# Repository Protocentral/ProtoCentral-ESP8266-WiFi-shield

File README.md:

ProtoCentral ESP8266 WiFi shield 
==================================
 [  
*ProtoCentral ESP8266 WiFi shield (PC-4356)*](https://www.protocentral.com/arduino-shields/944-protocentral-esp8266-wifi-shieldstandalone-for-arduino.html)
 
The ESP8266 WiFi chip has taken the IoT world by storm by breaking the cost barrier and making the IoT truly possible. The ProtoCentral ESP8266 WiFi shield is an easy and quick way to add WiFi functionality to your Arduino.
This board can be used an Arduino shield as well as a standalone breakout board if you prefer to program the ESP8266 directly. The onboard FT230X USB-to-UART circuit allows direct access to to the ESP 8266 module's UART interface. This allows programming of the ESP8266 chip's onboard processor to run the application itself without the need for an Arduino.
The module comes pre-flashed with the ESP8266 AT command set firmware. 

Features Overload!
-------------------
*	Slide switch - Serial communication support to work on ESP module individually
*	Firmware upgrade for ESP through USB
*	On board FTDI
*	Onboard regulator 3.3v with 800mA
*	Can be powered on/off using USB or from the Arduino board 
*	Board is pre-flashed  with an AT command set firmware and the same can be used to control ESP8266 module
*	Extra ESP8266 pins broken out for any additional usage requirements
*	802.11 b/g/n
*	Wi-Fi Direct (P2P), soft-AP
*	Integrated TCP/IP protocol stack

Includes:
----------
* Shield with the headers

Repository Contents
-------------------
* **/Firmware**  - Firmware and bin files for ESP8266
* **/Libraries** - Arduino library and example sketches.
* **/Hardware**  - All Eagle design files (.brd, .sch)

License Information
-------------------
This product is open source!

Please use, reuse, and modify these files as you see fit. Please maintain attribution to Protocentral and release anything derivative under the same license.

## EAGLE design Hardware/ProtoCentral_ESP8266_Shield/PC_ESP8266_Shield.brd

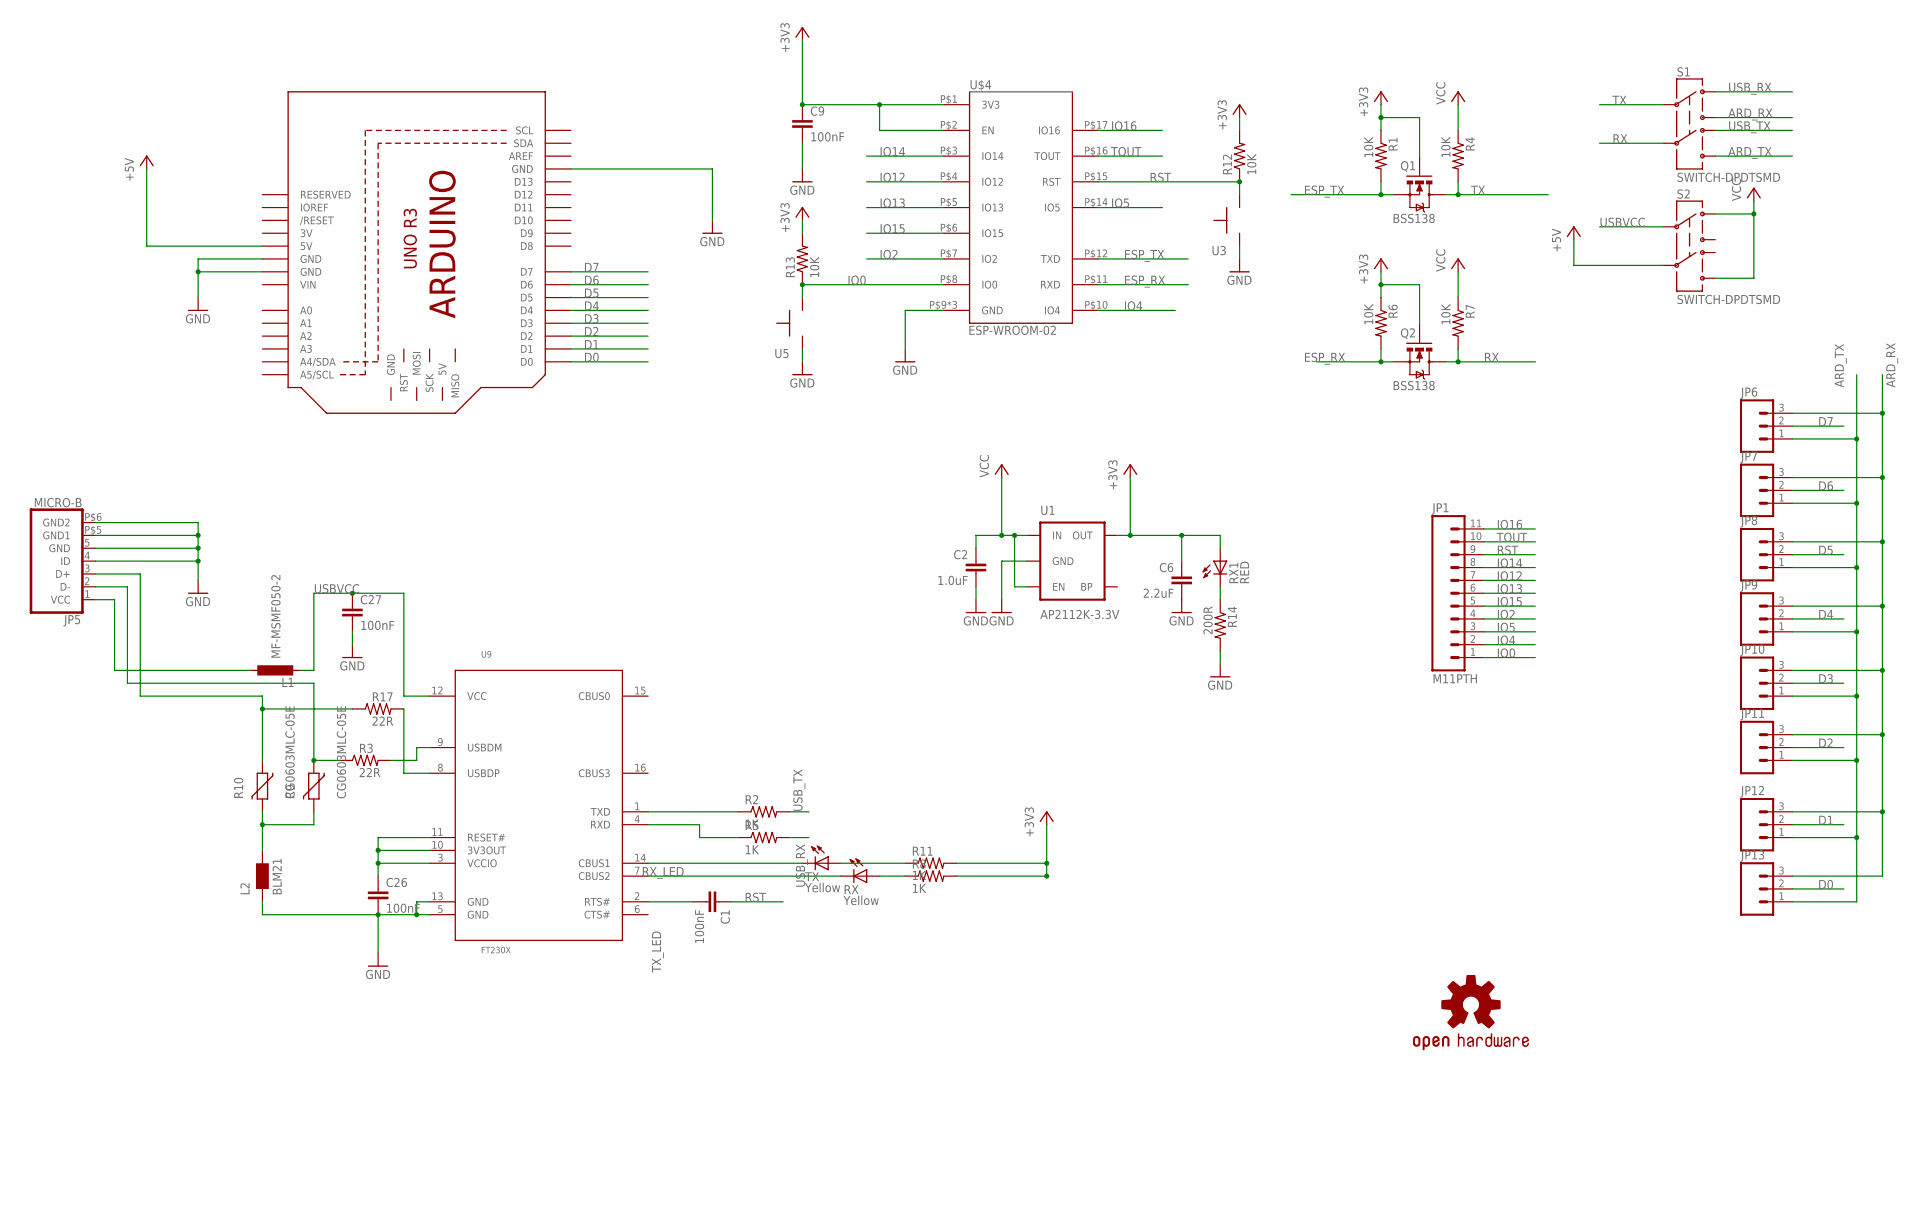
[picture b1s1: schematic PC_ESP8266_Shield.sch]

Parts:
C1, C9, C26, C27: 100nF; C0805
C2: 1.0uF; 0805
C6: 2.2uF; C0805
JP1: M11PTH; 1X11
JP5: MICRO-B
JP6, JP7, JP8, JP9, JP10, JP11, JP12, JP13: M03PTH; 1X03
L1: MF-MSMF050-2; L1812
L2: BLM21; 0805
Q1, Q2: BSS138; SOT23-3
R1, R4, R6, R7, R12, R13: 10K; R0805
R2, R5, R8, R11: 1K; R0805
R3, R17: 22R; R0805
R9, R10: CG0603MLC-05E; CT/CN0603
R14: 200R; R0805
RX: Yellow; CHIPLED_0603
RX1: RED; CHIPLED_0603
S1, S2: SWITCH-DPDTSMD; AYZ0202
TX: Yellow; CHIPLED_0603
U1: AP2112K-3.3V; SOT23-5
U3, U5: B3U-1000P
U9: FT230X; SSOP_16
U$1: ARDUINO
U$3: PROTY-LOGO; LOGO-PROTY
U$4: ESP-WROOM-02
U$5: OSHW-LOGOS; OSHW-LOGO-S

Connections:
3V: U$1.3V
+3V3: C6.1, C9.1, Q1.1 (G), Q2.1 (G), R1.1, R6.1, R8.2, R11.2, R12.2, R13.2, RX1.A, U1.5 (OUT), U$4.P$1 (3V3), U$4.P$2 (EN)
+5V: S2.5, U$1.5V
ARD_RX: JP6.3, JP7.3, JP8.3, JP9.3, JP10.3, JP11.3, JP12.3, JP13.3, S1.3
ARD_TX: JP6.1, JP7.1, JP8.1, JP9.1, JP10.1, JP11.1, JP12.1, JP13.1, S1.6
D0: JP13.2, U$1.D0
D1: JP12.2, U$1.D1
D2: JP11.2, U$1.D2
D3: JP10.2, U$1.D3
D4: JP9.2, U$1.D4
D5: JP8.2, U$1.D5
D6: JP7.2, U$1.D6
D7: JP6.2, U$1.D7
ESP_RX: Q2.2 (S), R6.2, U$4.P$11 (RXD)
ESP_TX: Q1.2 (S), R1.2, U$4.P$12 (TXD)
GND: C2.2, C6.2, C9.2, C26.2, C27.2, JP5.4 (ID), JP5.5 (GND), JP5.P$5 (GND1), JP5.P$6 (GND2), L2.1, R14.2, U1.2 (GND), U3.P$1, U5.P$1, U9.5 (GND), U9.13 (GND), U$1.GND, U$1.GND@1 (GND), U$1.GND@2 (GND), U$4.P$9 (GND), U$4.P$13 (GND), U$4.P$18 (GND)
IO0: JP1.1, R13.1, U5.P$2, U$4.P$8 (IO0)
IO2: JP1.4, U$4.P$7 (IO2)
IO4: JP1.2, U$4.P$10 (IO4)
IO5: JP1.3, U$4.P$14 (IO5)
IO12: JP1.7, U$4.P$4 (IO12)
IO13: JP1.6, U$4.P$5 (IO13)
IO14: JP1.8, U$4.P$3 (IO14)
IO15: JP1.5, U$4.P$6 (IO15)
IO16: JP1.11, U$4.P$17 (IO16)
unnamed: R2.1, U9.1 (TXD)
unnamed: C1.2, U9.2 (RTS#)
unnamed: R5.1, U9.4 (RXD)
unnamed: R8.1, RX.A
unnamed: R11.1, TX.A
unnamed: JP5.1 (VCC), L1.1
unnamed: R14.1, RX1.C
unnamed: R3.2, U9.9 (USBDM)
unnamed: C26.1, U9.3 (VCCIO), U9.10 (3V3OUT), U9.11 (RESET#)
unnamed: JP5.2 (D-), R3.1, R9.1
unnamed: R17.2, U9.8 (USBDP)
unnamed: L2.2, R9.2, R10.2
unnamed: JP5.3 (D+), R10.1, R17.1
RST: C1.1, JP1.9, R12.1, U3.P$2, U$4.P$15 (RST)
RX: Q2.3 (D), R7.2, S1.5
RX_LED: RX.C, U9.7 (CBUS2)
TOUT: JP1.10, U$4.P$16 (TOUT)
TX: Q1.3 (D), R4.2, S1.2
TX_LED: TX.C, U9.14 (CBUS1)
USBVCC: C27.1, L1.2, S2.2, U9.12 (VCC)
USB_RX: R5.2, S1.1
USB_TX: R2.2, S1.4
VCC: C2.1, R4.1, R7.1, S2.1, S2.6, U1.1 (IN), U1.3 (EN)
VIN: U$1.VIN

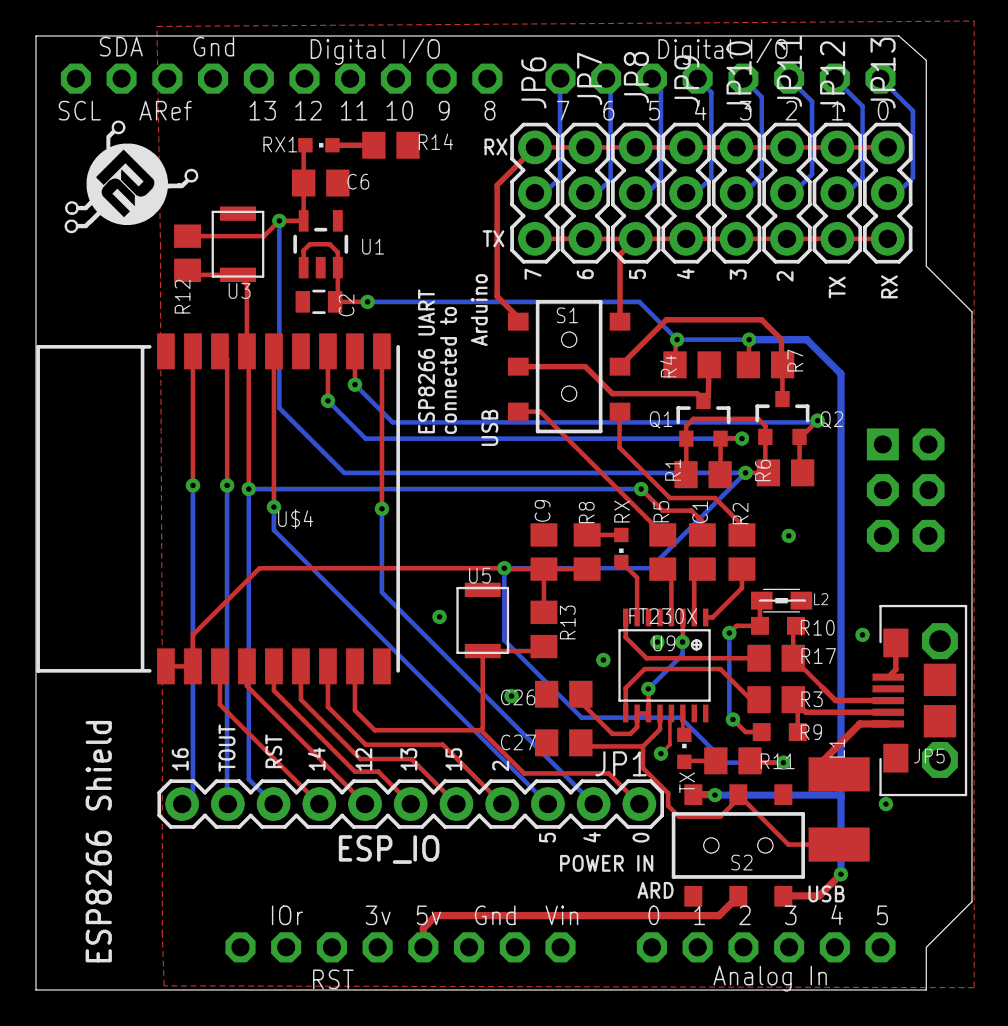
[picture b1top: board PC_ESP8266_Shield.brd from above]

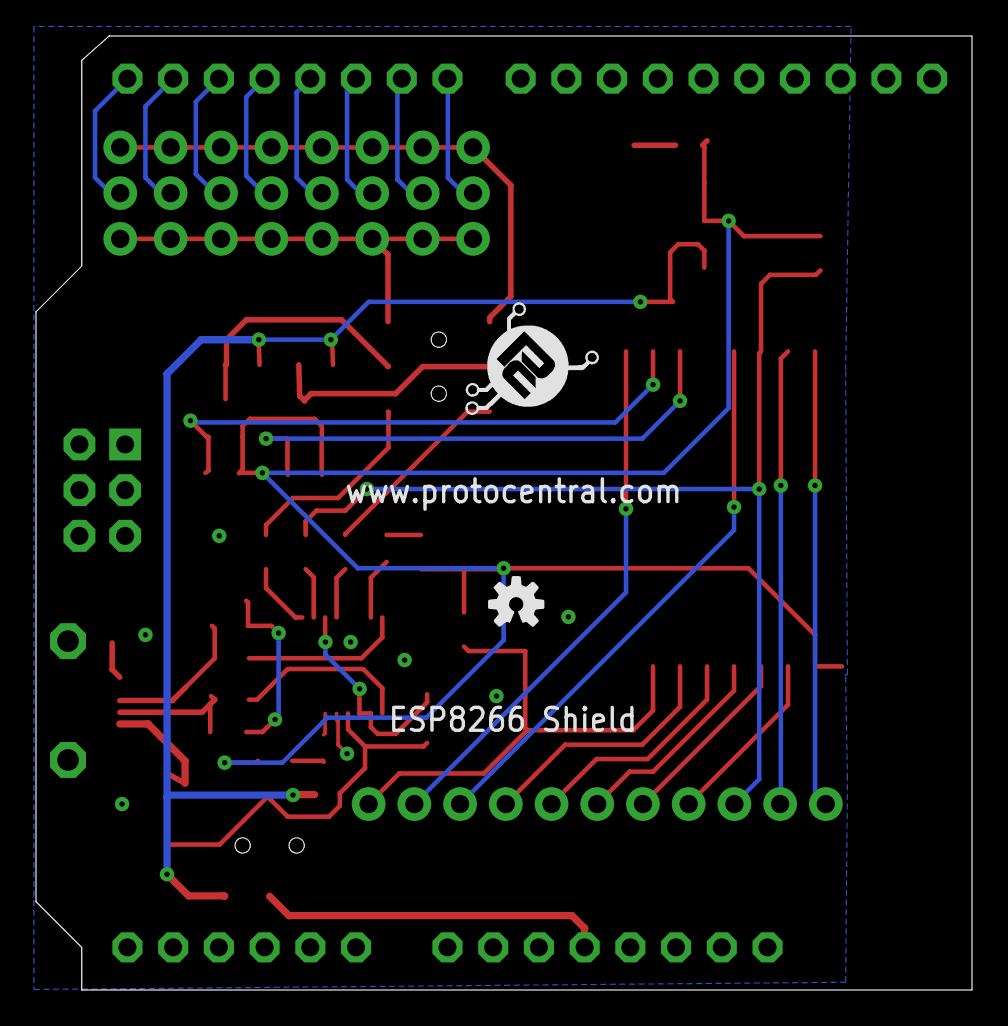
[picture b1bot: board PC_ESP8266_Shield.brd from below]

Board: 4 copper layers, 52.0 x 53.0 mm, 49 parts (2 on the bottom side), 47 nets.

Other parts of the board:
U$2: PROTY-LOGO; LOGO-PROTY

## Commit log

2015-11-05 Firmware for ESP8266 module
2015-11-05 Design File
2015-11-05 Arduino source code and example sketches

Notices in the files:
parts and their libraries:
SparkFun-Capacitors: Licensing: Creative Commons ShareAlike 4.0 International - https://creativecommons.org/licenses/by-sa/4.0
